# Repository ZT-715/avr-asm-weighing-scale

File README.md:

### AVR Microcontroller-Based Load Cell System

#### Project Overview and Highlights
This project demonstrates a microcontroller-based digital weighing system using an **ATMEGA328P**, developed entirely in **AVR-ASM**. The system features two custom-designed PCBs:
- ATMEGA328p devboard: 20x4 LCD, 3 buttons to show information in kilograms, pounds, and use the tare function, A/D AVcc filter, and an ICSP (In-Circuit Serial Programming).
- High-gain instrumental amplifier: allows weight measurement down to 5 kg ± 5g with a 30 Kg weight cell on the same 7.5V power source as the devboard, with noise filters to maximize A/D range and precision.
- All assembly routines are structured into independent files like timer, ADC, and display control routines.
- Even with TARE, the system shows "OVRW" indicator for overload scenarios.

#### Key Features
1. **Microcontroller and Programming:**
   - Developed using AVRASM2 assembler within MPLab IDE.
   - Programmed with USB-ASP and serial programming connector.
2. **Weight Calibration and Display:**
   - Linear calibration using the TARE button on the devboard and gain adjustments on the amplifier.
   - Precise weight display through precomputed lookup tables for kilograms and pounds.
3. **ADC Integration:**
   - 80%  range of 10-bit ADC of the ATMEGA328P (1-5 volts).
   - Conversion synchronized with Timer 1 for consistent 1 LCD update per
     second.
   - Filtering implemented as per manufacturer instructions on AVcc to reduce noise.
4. **Load Cell Signal Amplification:**
   - Differential output signal amplified with adjustable gain up to 3000 for
     scale adjustment.
   - Offset compensation to overcome amp. op. dead zone around 1V from GND.

#### Results and Next Steps

The system accurately measures weights within the defined range and seamlessly switches between lbs and kgs.
Future improvements include integrating all components into a single PCB, replacing the LCD with a smaller display, and designing a housing for the system. The system may also be battery-powered with efficient use of the ATMEGA328P's sleep states.

#### References
1. [Microchip AVR Microcontroller Hardware Design Considerations](https://ww1.microchip.com/downloads/en/Appnotes/AN2519-AVR-Microcontroller-Hardware-Design-Considerations-00002519B.pdf)
2. [ATMEGA328P Datasheet](https://ww1.microchip.com/downloads/en/DeviceDoc/Atmel-7810-Automotive-Microcontrollers-ATmega328P_Datasheet.pdf)
3. [AVR Instruction Set Manual](https://ww1.microchip.com/downloads/en/DeviceDoc/AVR-InstructionSet-Manual-DS40002198.pdf)
4. [Load Cell Basics](https://en.wikipedia.org/wiki/Load_cell)

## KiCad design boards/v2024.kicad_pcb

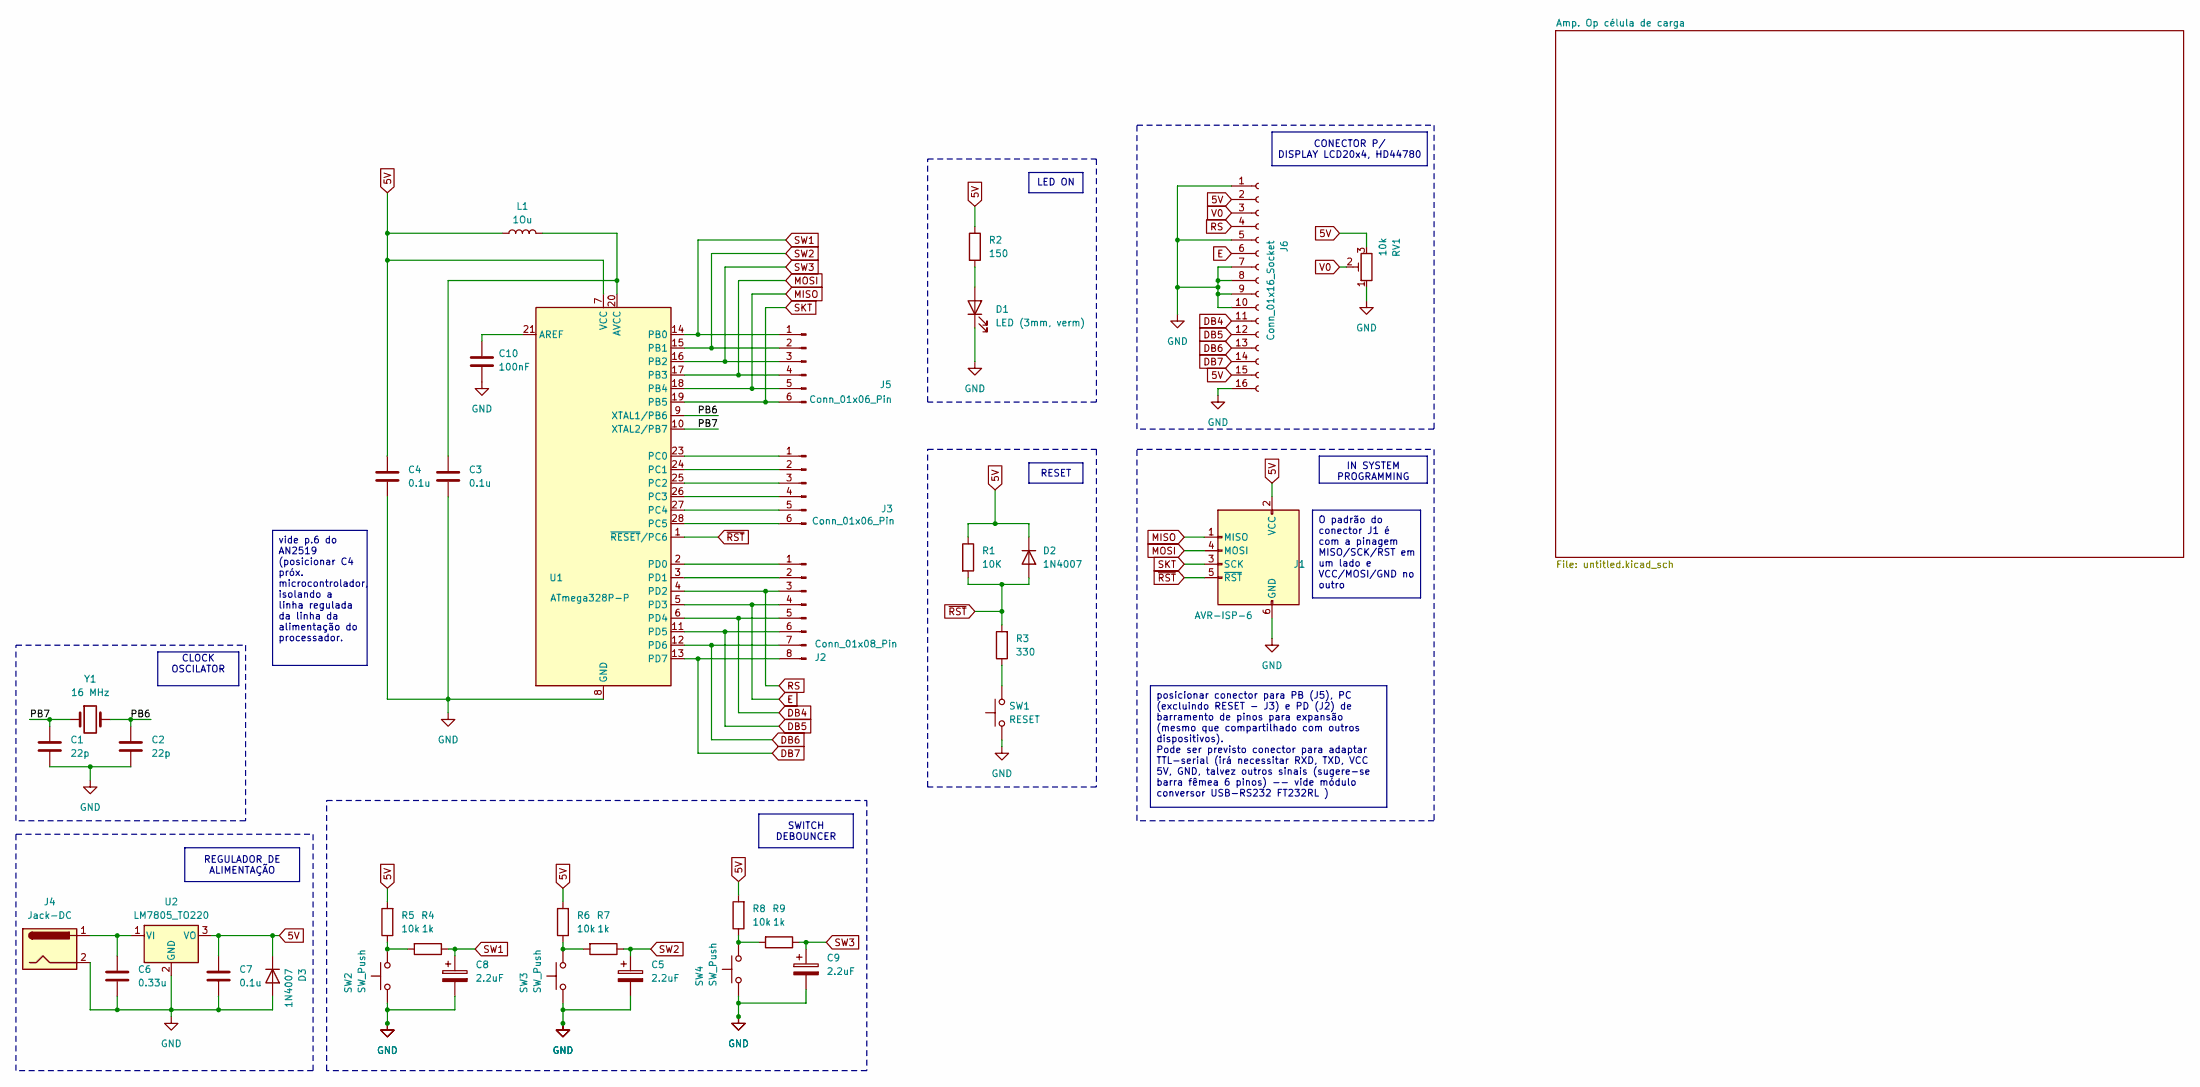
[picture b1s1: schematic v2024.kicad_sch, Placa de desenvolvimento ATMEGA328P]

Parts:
C1, C2: 22p; C_Disc_D3.4mm_W2.1mm_P2.50mm
C3, C4, C7: 0.1u; C_Disc_D3.4mm_W2.1mm_P2.50mm
C5, C8, C9: 2.2uF; CP_Radial_D5.0mm_P2.00mm
C6: 0.33u; C_Disc_D3.4mm_W2.1mm_P2.50mm
C10: 100nF; C_Disc_D3.4mm_W2.1mm_P2.50mm
D1: LED (3mm, verm); LED_D3.0mm
D2, D3: 1N4007; D_DO-41_SOD81_P10.16mm_Horizontal
J1: AVR-ISP-6; IDC-Header_2x03_P2.54mm_Vertical
J2: Conn_01x08_Pin; PinHeader_1x08_P2.54mm_Vertical
J3, J5: Conn_01x06_Pin; PinHeader_1x06_P2.54mm_Vertical
J4: Jack-DC; TerminalBlock_bornier_kre-2_P5.08mm
J6: Conn_01x16_Socket; PinHeader_1x16_P2.54mm_Vertical
L1: 1Ou; L_Radial_D10.0mm_P5.00mm_Fastron_07M
R1: 10K; R_Axial_DIN0204_L3.6mm_D1.6mm_P5.08mm_Horizontal
R2: 150; R_Axial_DIN0204_L3.6mm_D1.6mm_P5.08mm_Horizontal
R3: 330; R_Axial_DIN0204_L3.6mm_D1.6mm_P5.08mm_Horizontal
R4, R7, R9: 1k; R_Axial_DIN0204_L3.6mm_D1.6mm_P1.90mm_Vertical
R5, R6, R8: 10k; R_Axial_DIN0204_L3.6mm_D1.6mm_P1.90mm_Vertical
RV1: 10k; Potentiometer_Bourns_3296W_Vertical
SW1: RESET; SW_PUSH_6mm_H5mm
SW2, SW3, SW4: SW_Push; SW_PUSH_6mm_H5mm
U1: ATmega328P-P; DIP-28_W7.62mm_w_Socket
U2: LM7805_TO220; TO-220-3_Vertical
Y1: 16 MHz; Crystal_HC49-4H_Vertical

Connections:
5V: C4.1, C7.1, D2.1 (K), D3.1 (K), J1.2 (VCC), J6.2, J6.15, L1.1, R1.1, R2.1, R5.2, R6.2, R8.2, RV1.3, U1.7 (VCC), U2.3 (VO)
/PB6: C2.1, U1.9 (XTAL1/PB6), Y1.2
/PB7: C1.1, U1.10 (XTAL2/PB7), Y1.1
DB4: J2.5, J6.11, U1.6 (PD4)
DB5: J2.6, J6.12, U1.11 (PD5)
DB6: J2.7, J6.13, U1.12 (PD6)
DB7: J2.8, J6.14, U1.13 (PD7)
E: J2.4, J6.6, U1.5 (PD3)
GND: C1.2, C2.2, C3.2, C4.2, C5.2, C6.2, C7.2, C8.2, C9.2, C10.2, D1.1 (K), D3.2 (A), J1.6 (GND), J4.2, J6.1, J6.5, J6.7, J6.8, J6.9, J6.10, J6.16, RV1.1, SW1.1, SW2.1, SW3.1, SW4.1, U1.8 (GND), U1.22 (GND), U2.2 (GND); also elsewhere on the board
MISO: J1.1 (MISO), J5.5, U1.18 (PB4)
MOSI: J1.4 (MOSI), J5.4, U1.17 (PB3)
unnamed: D1.2 (A), R2.2
unnamed: J2.1, U1.2 (PD0)
unnamed: J2.2, U1.3 (PD1)
unnamed: J3.1, U1.23 (PC0)
unnamed: J3.2, U1.24 (PC1)
unnamed: J3.3, U1.25 (PC2)
unnamed: J3.4, U1.26 (PC3)
unnamed: J3.5, U1.27 (PC4)
unnamed: J3.6, U1.28 (PC5)
unnamed: R3.1, SW1.2
unnamed: R4.2, R5.1, SW2.2
unnamed: R6.1, R7.2, SW3.2
unnamed: R8.1, R9.2, SW4.2
unnamed: C10.1, U1.21 (AREF)
unnamed: C3.1, L1.2, U1.20 (AVCC)
unnamed: C6.1, J4.1, U2.1 (VI)
RS: J2.3, J6.4, U1.4 (PD2)
SKT: J1.3 (SCK), J5.6, U1.19 (PB5)
SW1: C8.1, J5.1, R4.1, U1.14 (PB0)
SW2: C5.1, J5.2, R7.1, U1.15 (PB1)
SW3: C9.1, J5.3, R9.1, U1.16 (PB2)
V0: J6.3, RV1.2
~RST: D2.2 (A), J1.5 (~RST), R1.2, R3.2, U1.1 (~RESET/PC6)

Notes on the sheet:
O padrão do conector J1 é com a pinagem MISO/SCK/RST em um lado e VCC/MOSI/GND no outro
CLOCK OSCILATOR
IN SYSTEM PROGRAMMING
posicionar conector para PB (J5), PC (excluindo RESET - J3) e PD (J2) de barramento de pinos para expansão (mesmo que compartilhado com outros dispositivos). Pode ser previsto conector para adaptar TTL-serial (irá necessitar RXD, TXD, VCC 5V, GND, talvez outros sinais (sugere-se barra fêmea 6 pinos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
LED ON
RESET
vide p.6 do AN2519 (posicionar C4 próx. microcontrolador, isolando a linha regulada da linha da alimentação do processador.
REGULADOR DE ALIMENTAÇÃO
CONECTOR P/ DISPLAY LCD20x4, HD44780
SWITCH DEBOUNCER

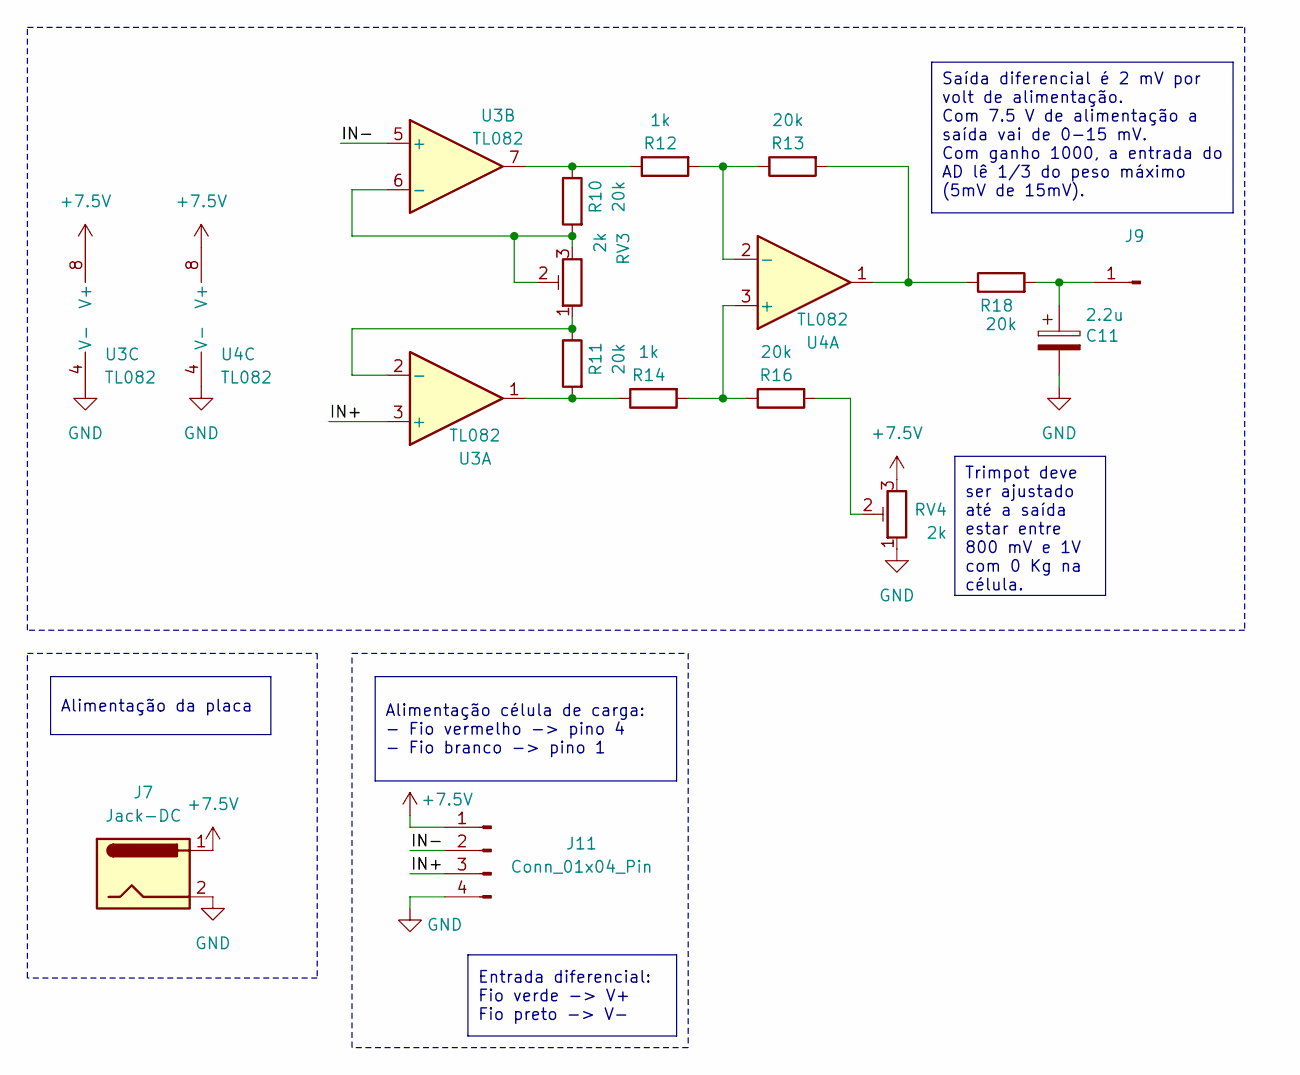
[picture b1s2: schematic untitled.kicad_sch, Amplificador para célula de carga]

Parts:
C11: 2.2u; CP_Radial_D5.0mm_P2.50mm
J7: Jack-DC; TerminalBlock_bornier_kre-2_P5.08mm
J9: wheigh_out 0.0-5.0V; PinHeader_1x01_P2.54mm_Vertical
J11: Conn_01x04_Pin; PinHeader_1x04_P2.54mm_Vertical
R10, R11, R13, R16, R18: 20k; R_Axial_DIN0207_L6.3mm_D2.5mm_P7.62mm_Horizontal
R12, R14: 1k; R_Axial_DIN0207_L6.3mm_D2.5mm_P7.62mm_Horizontal
RV3, RV4: 2k; Potentiometer_Bourns_3296W_Vertical
U3, U4: TL082; DIP-8_W7.62mm_Socket

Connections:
+7.5V: J7.1, J11.1, RV4.3, U3.8 (V+), U4.8 (V+)
/Amp. Op célula de carga/IN+: J11.3, U3.3 (+)
/Amp. Op célula de carga/IN-: J11.2, U3.5 (+)
GND: C11.2, J7.2, J11.4, RV4.1, U3.4 (V-), U4.4 (V-); also elsewhere on the board
unnamed: C11.1, J9.1, R18.2
unnamed: R10.1, R12.1, U3.7
unnamed: R11.2, R14.1, U3.1
unnamed: R13.2, R18.1, U4.1
unnamed: R16.2, RV4.2
unnamed: R11.1, RV3.1, U3.2 (-)
unnamed: R10.2, RV3.2, RV3.3, U3.6 (-)
unnamed: R14.2, R16.1, U4.3 (+)
unnamed: R12.2, R13.1, U4.2 (-)

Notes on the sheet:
Alimentação célula de carga: - Fio vermelho -> pino 4 - Fio branco -> pino 1
Alimentação da placa
Trimpot deve ser ajustado até a saída estar entre 800 mV e 1V com 0 Kg na célula.
Saída diferencial é 2 mV por volt de alimentação. Com 7.5 V de alimentação a saída vai de 0-15 mV. Com ganho 1000, a entrada do AD lê 1/3 do peso máximo (5mV de 15mV).
Entrada diferencial: Fio verde -> V+ Fio preto -> V-

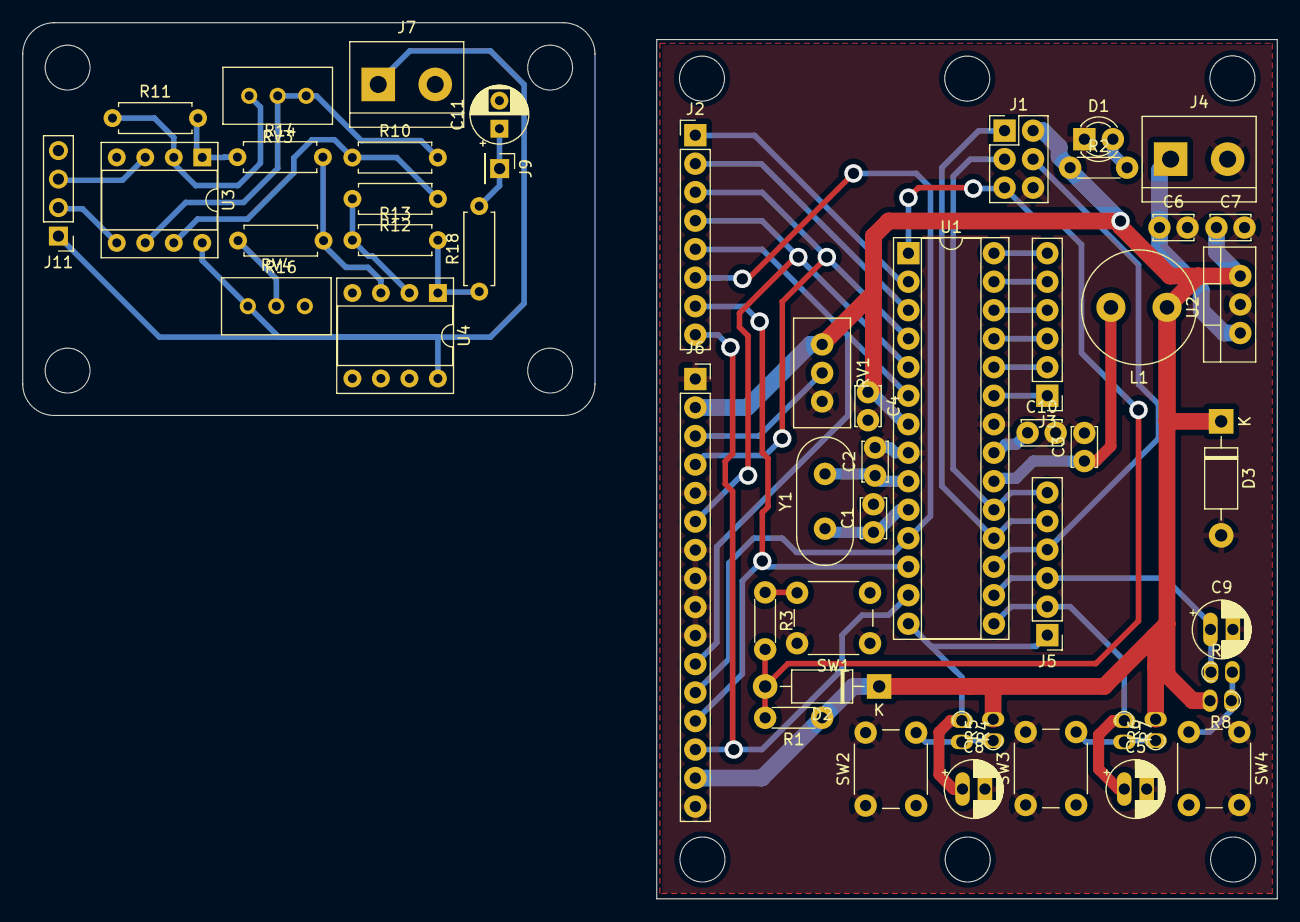
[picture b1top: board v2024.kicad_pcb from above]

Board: 2 copper layers, 111.8 x 78.1 mm, 52 parts (0 on the bottom side), 46 nets.

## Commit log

2024-11-12 Init project: electronic weighting scale
2024-11-16 Change project to multiple files
2024-11-16 Add AD configuration
2024-11-16 Display & configure AD on single read mode
2024-11-17 Convert and print AD read to BCD value on LCD
2024-11-21 Put isr in different file
2024-11-21 Add functional TARE function
2024-11-21 Switches file
2024-11-26 Change switch handler to return instead of loop
    Now the handler checks the switches, if they are still
    being pressed, then the handler just returns and main
    loop can continue to execute.
2024-11-26 Clean AD_tare code
2024-11-26 Define weight sample rate with timer and polling
    TODO:
    Implement AD read with interrupts to increase
    sample rate precision, independently of main
    loop routines
2024-11-26 Fix flag clear for sample rate pulling
2024-11-26 Add AD interrupt based sampling 16 kHz
2024-11-30 Change ADC to righ justified
2024-11-30 Add LUT generator for Kg and Lbs with 1024 values
2024-12-01 Fix LUT gen: add .db after labels
2024-12-01 Change sample rate to 15.625 KHz, instead of 244 Hz
2024-12-01 Change lut to fixed size strings
2024-12-01 Implement LUT for Kg and display (tested)
2024-12-01 Add switch between lbs and kgs
2024-12-01 Change sample rate to 16Mhz/256/1024 = 61 Hz
2024-12-01 Change sample rate to 61 Hz
2024-12-01 Change sample rate to 1s
2024-12-01 Hide cursor from LCD
2024-12-01 Change TARE to Portuguese
2024-12-02 Add safety: 5V in ADC => OVRW on screen
    OVRW is writen independently of TARE
2024-12-02 Clean screen0 subroutine
2024-12-11 Add board KiCad design
2024-12-11 Add README.md
2024-12-11 Add images from the boards and final test
2024-12-11 Add images of the boards and final build
2024-12-11 Change image position on README
2024-12-11 Fix README title
